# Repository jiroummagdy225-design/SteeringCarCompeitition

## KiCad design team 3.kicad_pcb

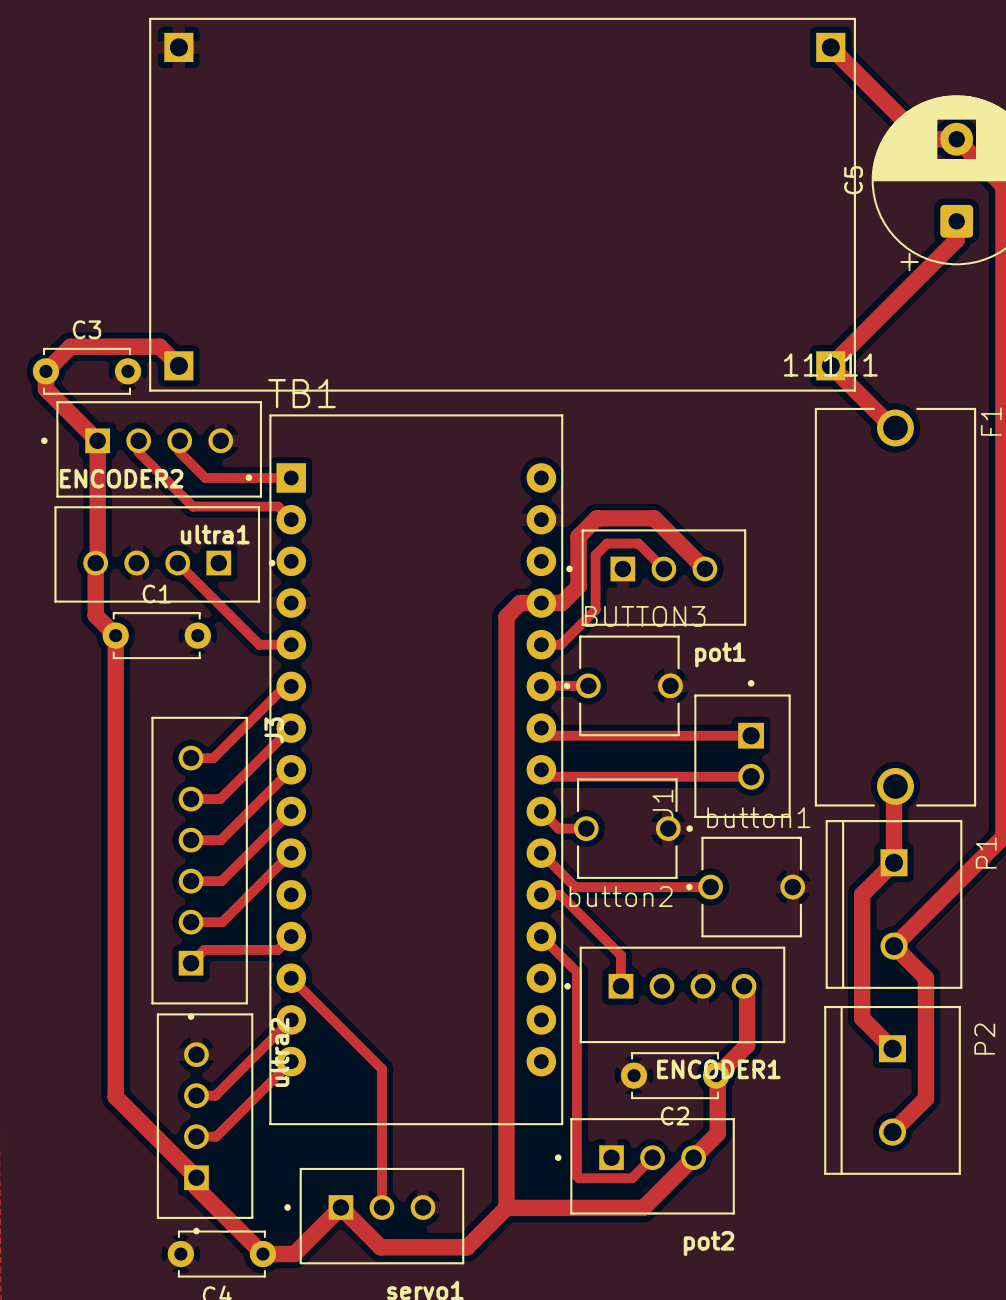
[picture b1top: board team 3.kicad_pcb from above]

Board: 2 copper layers, 22 parts (0 on the bottom side), 26 nets.

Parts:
11111: LM2596
BUTTON3: SW_BUTT-2
C1, C2, C3, C4: C; C_Disc_D5.0mm_W2.5mm_P5.00mm
C5: C; CP_Radial_D10.0mm_P5.00mm
ENCODER1, ENCODER2: JST_B4B-XH-A(LF)(SN)
F1: FUSE_4527
J1: JST_B2B-XH-A(LF)(SN)
J3: JST_B6B-XH-A(LF)(SN)
P1, P2: TE_282837-2
TB1: SHIELD_ARDUINO_NANO
button1, button2: SW_BUTT-2
pot1, pot2: JST_B3B-XH-A_(LF)(SN)
servo1: JST_B3B-XH-A_(LF)(SN)
ultra1, ultra2: JST_B4B-XH-A(LF)(SN)

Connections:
+12V: F1.2, P1.1, P2.1
/0: J3.5, TB1.7 (D4)
/1: J3.4, TB1.8 (D5)
/2: J3.3, TB1.9 (D6)
/4: J3.2, TB1.10 (D7)
/6: TB1.13 (D10), servo1.2
/14: ENCODER2.2, TB1.5 (D2)
/15: ENCODER1.1, TB1.20 (A1)
/16: TB1.21 (A2), button1.1
/A0: TB1.22 (A3), button2.2
/A1: TB1.26 (A7), pot1.2
/A6: TB1.19 (A0), pot2.2
/B3: BUTTON3.1, TB1.25 (A6)
/ENA: J3.6, TB1.6 (D3)
/ENB: J3.1, TB1.12 (D9)
/LCP1: J1.2, TB1.23 (A4)
/LCP2: J1.1, TB1.24 (A5)
/echo7: TB1.1 (D1/TX), ultra1.3
/echo12: TB1.14 (D11/MOSI), ultra2.3
/trig8: TB1.2 (D0/RX), ultra1.2
/trig13: TB1.15 (D12/MISO), ultra2.2
GND: 11111.OUT-, BUTTON3.2, C1.2, C2.2, C3.2, C4.2, ENCODER1.3, ENCODER2.3, TB1.4 (COM/GND), TB1.29 (COM/GND), button1.2, button2.1, pot1.1, pot2.1, servo1.3, ultra1.4, ultra2.4
GND1: 11111.IN-, C5.2, P1.2, P2.2
unnamed: 11111.IN+, C5.1, F1.1
unnamed: TB1.3 (RESET), TB1.28 (RESET)
VCC: 11111.OUT+, C1.1, C2.1, C3.1, C4.1, ENCODER1.4, ENCODER2.4, TB1.27 (+5V), pot1.3, pot2.3, servo1.1, ultra1.1, ultra2.1
